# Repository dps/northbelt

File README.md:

northbelt
=========

A belt that buzzes north

This repo contains Arduino code for a wearable compass, consisting of a belt with a number of mobile phone vibration motors mounted along its circumference.  As the wearer moves around, the motor closest to magnetic north buzzes.  According to [this WIRED article](http://archive.wired.com/wired/archive/15.04/esp.html), through the miracle of [brain plasticity](http://en.wikipedia.org/wiki/Neuroplasticity), this will give the gift of an amazing sixth sense of direction.

Hardware
========

Prototype
---------
 * [A-Star 32U4 Mini ULV](http://www.pololu.com/product/3102)
 * [LSM303D 3D Compass and Accelerometer breakout](http://www.pololu.com/product/2127)
 * [LiPoly charger](http://www.adafruit.com/products/259)
 * [Lithium Ion Polymer Battery - 3.7v 500mAh](http://www.adafruit.com/products/1578)
 * [Vibrating Mini Motor Disc](http://www.adafruit.com/products/1201) x 16
 * Motor board x16
 * 20 way ribbon cable
 * [Belt](http://amzn.com/B001FOR2CY)

Pololu A-Star
-------------

[A* Pinout](http://www.pololu.com/file/0J784/a-star-32u4-mini-pinout.pdf)

    A*  <---> LS303
    -----------------------
    5V  <---> 5V
    GND <---> GND
    2   <---> SDA
    3   <---> SCL
    4   <---> 0 degree vibe
    5   <---> 22.5
    6   <---> 45
    7   <--->
    8   <---> 90
    9   <--->
    10  <---> 135
    11  <--->
    12  <---> 180
    13  <--->
    14  <---> 225
    15  <--->
    16  <---> 270
    17  <--->
    18  <---> 315
    19  <---> 337.5

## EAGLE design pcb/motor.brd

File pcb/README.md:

This directory contains EAGLE files for the schematic and PCB layout of the motor carrier boards.

The components (x2) for the motor board can be found in the mouser saved project located at http://www.mouser.com/ProjectManager/ProjectDetail.aspx?AccessID=1ebce4eb52

The PCB is available to order as a shared project on OSHPark at https://oshpark.com/shared_projects/lNbIvA7q .  Orders at OSHPark are in multiples of 3 so order 6x to get 18 boards for 16 points of the compass.

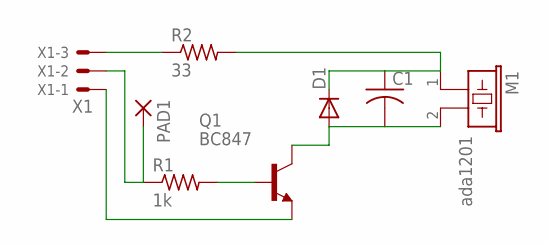
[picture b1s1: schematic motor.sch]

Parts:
C1: C-USC0603; C0603
D1: DIODE-DO214AC; DO214AC
M1: ada1201; B/C11L
PAD1: 1,6/0,8
Q1: BC847; SOT23
R1: 1k; R0805
R2: 33; R0805
X1: X1; 22-23-2031

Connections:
5V: R2.1, X1.3
GND: Q1.2 (E), X1.1
unnamed: PAD1.1, R1.1, X1.2
unnamed: Q1.1 (B), R1.2
unnamed: C1.2, D1.A, M1.2, Q1.3 (C)
unnamed: C1.1, D1.C, M1.1, R2.2

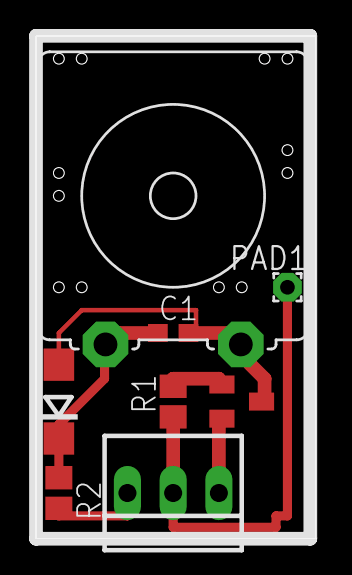
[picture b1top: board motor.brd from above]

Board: 2 copper layers, 15.5 x 27.9 mm, 8 parts (0 on the bottom side), 6 nets.

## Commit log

2014-08-19 Add lsm303-arduino as a submodule
2014-08-19 hookup
2014-08-19 Initial Arduino sketch
2014-08-19 fixup formatting
2014-08-19 initial vibe logic
2014-08-23 first prototype
2014-08-24 Use correct axis for orientation in belt. Factor out DEBUG code. Add fancy calibration UI.
2014-08-24 Read and write calibration data to EEPROM on the AVR
2014-09-01 Added PCB design for motor boards.
2014-09-02 Added an extra pad for the control signal on motor board.
2014-09-18 Add sewable drill holes to the motor board
